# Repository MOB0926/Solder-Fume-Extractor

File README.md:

# Solder-Fume-Extractor

# Why?

- I made this project because I needed a fan extarctor in general and thought it would be fun to just make one as a project for Blueprint, in my effrot to gain experience in engeneering and design.

# What?

- This project is my attempt at making a custom fume extractor using a 120mm pc fan and a custom PCB.
   
- In order to not waste a full MCU on just a fan I opted to add a few features and make this fan feature a rotary encoder, OLED display, and GPIO pins for working on projects.
        
- The fan and PCB are housed in a custom 3D-Printed case using some pc fan mounting screws
       
- My original goal with the design was to make it a economic as possible, but with the nesscesity of a custom PCB I opted instead to focus my main goal on hand-soldering the PCB, which is something I have been wanting to learn. 
        
# Case
       
- The design began with the case, which i brainstormed untill i developed a general idea in my head.
   
- Once i had a general idea I began taking measurements and designing every piece in Onshape.
   
- I started with the main body, keeping in mind space and acces to the PCB and a way to mount the fan.

- I whent with a panel at the bottom, and slots on the sides which would hold the post that supported the fan.

- After I was done with the base, I needed a way to mount the fan and add a filter to stop myself from touching the blades.
           
- I decided on a casing that would wrap around the fan and allow me to mount it to the posts, and a custom honey-comb filter

- Finally I inserted all my parts into an assembly where I put everything together

# PCB

- I made the case first in order to figure out the dimmensions of the PCB I would be able to include.
   
- My original idea was to use an rp2040 as I have experience with it and a very over complicated adjustable boost converter to power the fan, but it was too much for me and I was unable to verify it would work before finishing the project, so I completely restructured my PCB in a V2
     
- V2: This version is much more simple and includes all hand-solder friendly components in order to acomplish my goal. I opted for an ESP32 module and a basic 5 to 12 volt boost converter.

# Firmware
         
- This design does not require any firmare to work because of how the PCB works but you can digitally disable the fan through a mosfet (using IO6 on the MCU). I made google Gemini write me a quick c++ script for it which is placed in the code.txt file
       
- This board can use other languages like CircuitPython using the (ESP32-C3-Lyra V2.0 by Espressif) release as it uses the same MCU so it should work fine. But you can use whatever suits your project.

# Cost

- PCB: $2.10 (plus shipping)
- PCB Components: $19.19 (plus shipping)
- PC Fan: $10-$30 (or free if you have a spare one)
- PC Fan Mounting Screws: $5 (or free if you have a PC with spares)
- 3D-Printing Fillament: (unknown yet)

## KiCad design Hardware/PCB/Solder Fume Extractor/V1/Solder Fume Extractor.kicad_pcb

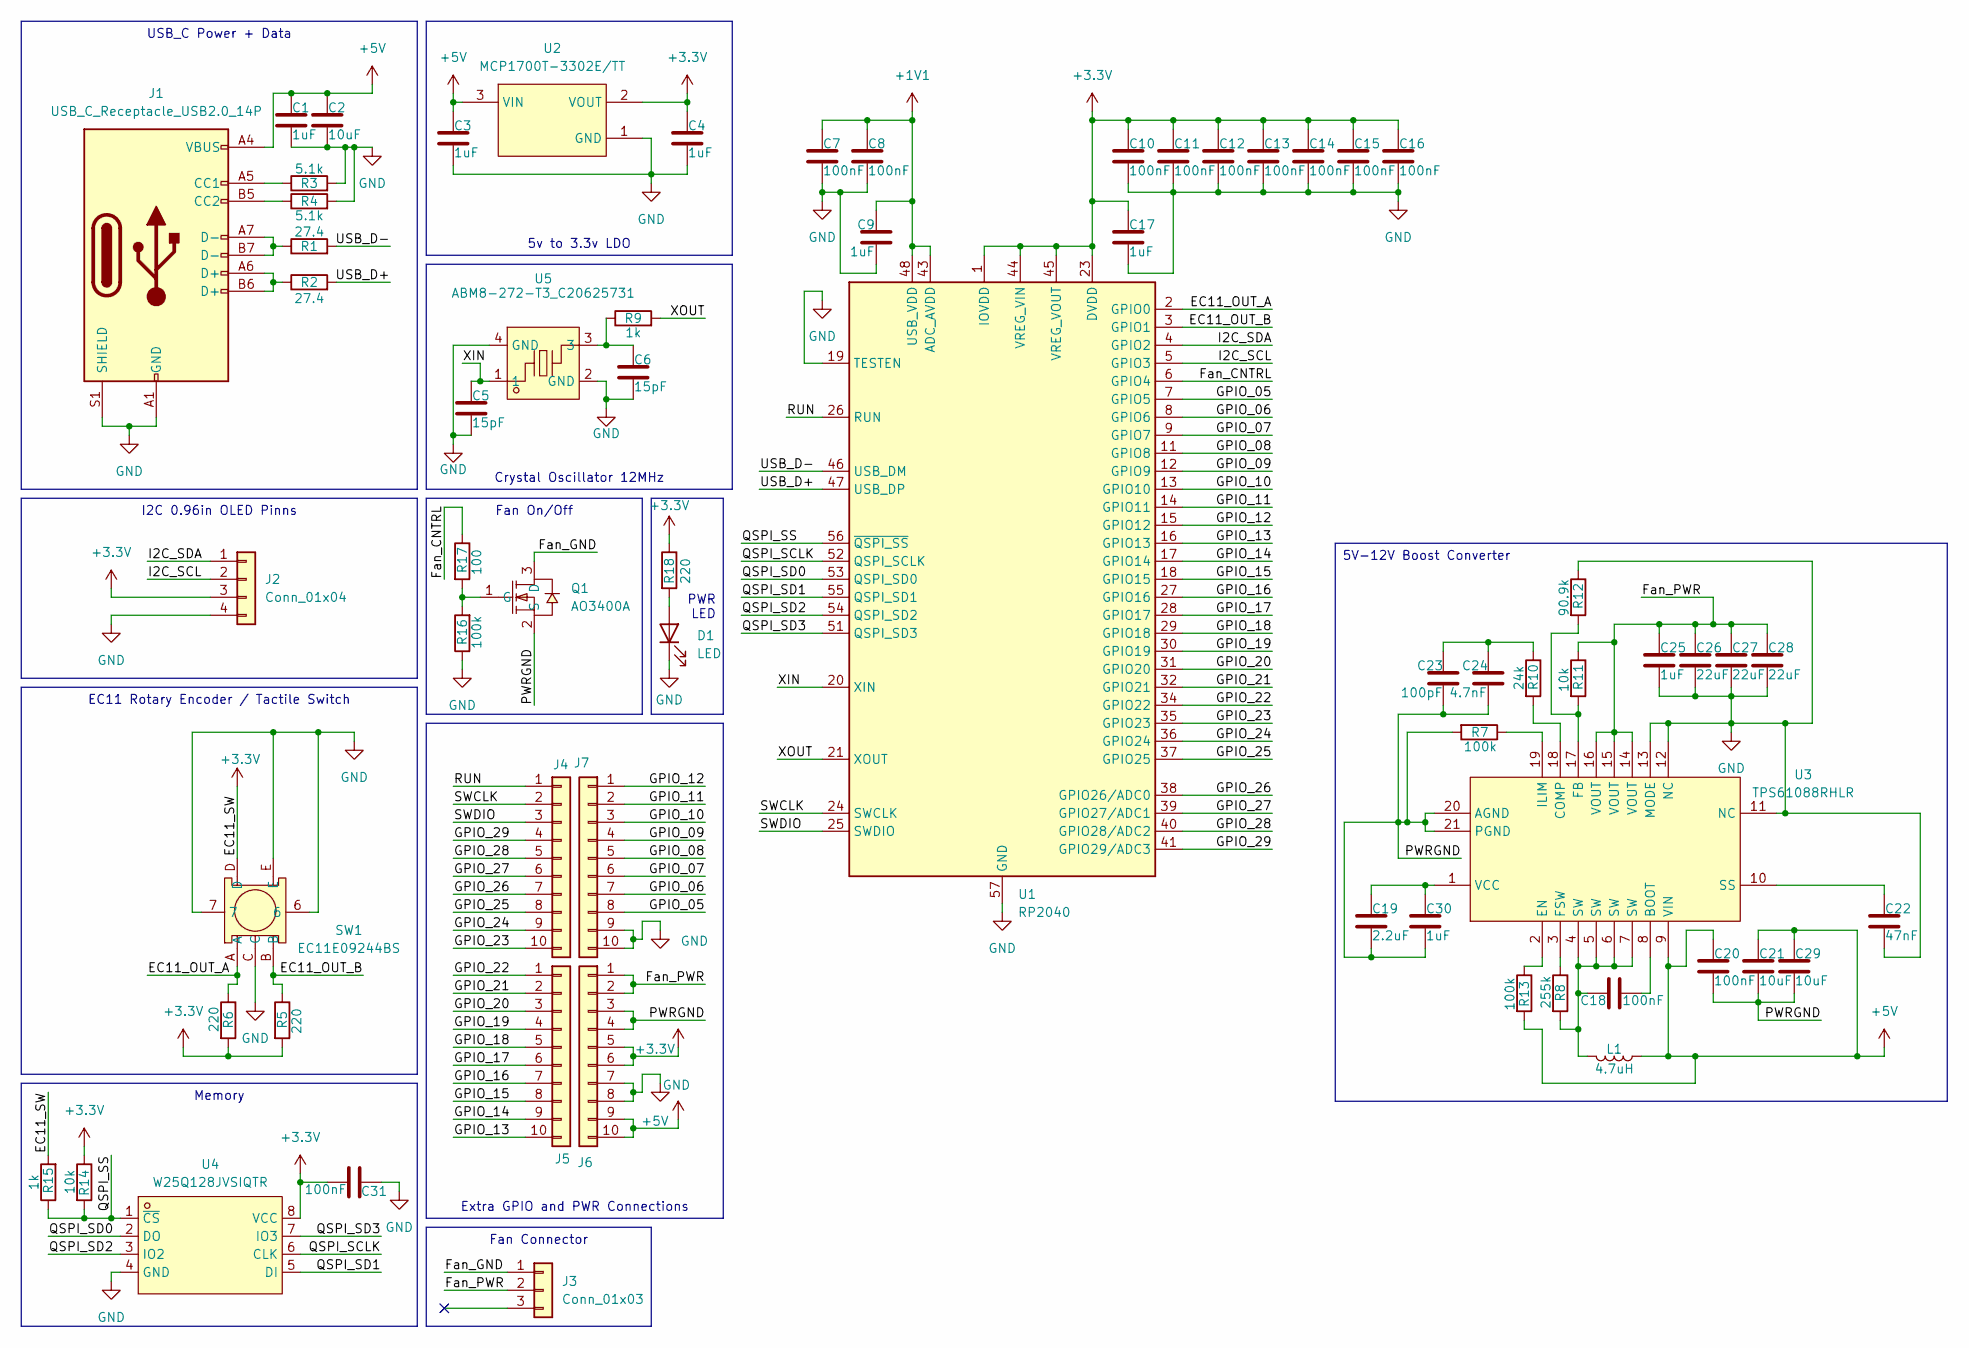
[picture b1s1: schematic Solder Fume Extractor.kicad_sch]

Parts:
C1, C3, C4, C9, C17, C25, C30: 1uF; C_0603_1608Metric
C2: 10uF; C_0603_1608Metric
C5, C6: 15pF; C_0603_1608Metric
C7, C8, C10, C11, C12, C13, C14, C15, C16, C18, C20, C31: 100nF; C_0603_1608Metric
C19: 2.2uF; C_0603_1608Metric
C21, C29: 10uF; C_1210_3225Metric
C22: 47nF; C_0603_1608Metric
C23: 100pF; C_0603_1608Metric
C24: 4.7nF; C_0603_1608Metric
C26, C27, C28: 22uF; C_1210_3225Metric
D1: LED; LED_0603_1608Metric
J1: USB_C_Receptacle_USB2.0_14P; USB_C_Receptacle_HRO_TYPE-C-31-M-12
J2: Conn_01x04; PinHeader_1x04_P2.54mm_Vertical
J3: Conn_01x03; PinHeader_1x03_P2.54mm_Vertical
J4, J5, J6, J7: Conn_01x10; PinHeader_1x10_P2.54mm_Vertical
L1: 4.7uH; L_Taiyo-Yuden_NR-60xx_HandSoldering
Q1: AO3400A; SOT-23-3_L2.9-W1.3-P1.90-LS2.4-BR; LCSC Part C20917
R1, R2: 27.4; R_0603_1608Metric
R3, R4: 5.1k; R_0603_1608Metric
R5, R6, R18: 220; R_0603_1608Metric
R7: 100k; C_0603_1608Metric
R8: 255k; R_0603_1608Metric
R9, R15: 1k; R_0603_1608Metric
R10: 24k; R_0603_1608Metric
R11, R14: 10k; R_0603_1608Metric
R12: 90.9k; R_0603_1608Metric
R13, R16: 100k; R_0603_1608Metric
R17: 100; R_0603_1608Metric
SW1: EC11E09244BS; SW-TH_EC11XXXXXXXX; LCSC Part C470742
U1: RP2040; QFN-56-1EP_7x7mm_P0.4mm_EP3.2x3.2mm
U2: MCP1700T-3302E/TT; SOT-23-3_L2.9-W1.6-P1.90-LS2.8-BR; LCSC Part C39051
U3: TPS61088RHLR; VQFN-20_L4.6-W3.6-P0.50-BL; LCSC Part C87357
U4: W25Q128JVSIQTR; SOIC-8_L5.3-W5.3-P1.27-LS8.0-BL; LCSC Part C97521
U5: ABM8-272-T3_C20625731; CRYSTAL-SMD_4P-L3.2-W2.5-BL; LCSC Part C20625731

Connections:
+1V1: C7.1, C8.1, C9.1, U1.43 (ADC_AVDD), U1.48 (USB_VDD)
+3.3V: C4.1, C10.1, C11.1, C12.1, C13.1, C14.1, C15.1, C16.1, C17.1, C31.2, J2.3, J6.5, J6.6, R5.2, R6.2, R14.1, R15.2, R18.1, SW1.D, U1.1 (IOVDD), U1.10 (IOVDD), U1.22 (IOVDD), U1.23 (DVDD), U1.33 (IOVDD), U1.42 (IOVDD), U1.44 (VREG_VIN), U1.45 (VREG_VOUT), U1.49 (IOVDD), U1.50 (DVDD), U2.2 (VOUT), U4.8 (VCC)
+5V: C1.1, C2.1, C3.1, C20.1, C21.1, C29.1, J1.A4 (VBUS), J1.A9 (VBUS), J1.B4 (VBUS), J1.B9 (VBUS), J6.9, J6.10, L1.2, R13.2, U2.3 (VIN), U3.9 (VIN)
/EC11_OUT_A: R6.1, SW1.A, U1.2 (GPIO0)
/EC11_OUT_B: R5.1, SW1.B, U1.3 (GPIO1)
/Fan_CNTRL: R17.1, U1.6 (GPIO4)
/Fan_GND: J3.1, Q1.3 (D)
/Fan_PWR: C25.1, C26.1, C27.1, C28.1, J3.2, J6.1, J6.2, R11.1, U3.14 (VOUT), U3.15 (VOUT), U3.16 (VOUT)
/GPIO_05: J7.8, U1.7 (GPIO5)
/GPIO_06: J7.7, U1.8 (GPIO6)
/GPIO_07: J7.6, U1.9 (GPIO7)
/GPIO_08: J7.5, U1.11 (GPIO8)
/GPIO_09: J7.4, U1.12 (GPIO9)
/GPIO_10: J7.3, U1.13 (GPIO10)
/GPIO_11: J7.2, U1.14 (GPIO11)
/GPIO_12: J7.1, U1.15 (GPIO12)
/GPIO_13: J5.10, U1.16 (GPIO13)
/GPIO_14: J5.9, U1.17 (GPIO14)
/GPIO_15: J5.8, U1.18 (GPIO15)
/GPIO_16: J5.7, U1.27 (GPIO16)
/GPIO_17: J5.6, U1.28 (GPIO17)
/GPIO_18: J5.5, U1.29 (GPIO18)
/GPIO_19: J5.4, U1.30 (GPIO19)
/GPIO_20: J5.3, U1.31 (GPIO20)
/GPIO_21: J5.2, U1.32 (GPIO21)
/GPIO_22: J5.1, U1.34 (GPIO22)
/GPIO_23: J4.10, U1.35 (GPIO23)
/GPIO_24: J4.9, U1.36 (GPIO24)
/GPIO_25: J4.8, U1.37 (GPIO25)
/GPIO_26: J4.7, U1.38 (GPIO26/ADC0)
/GPIO_27: J4.6, U1.39 (GPIO27/ADC1)
/GPIO_28: J4.5, U1.40 (GPIO28/ADC2)
/GPIO_29: J4.4, U1.41 (GPIO29/ADC3)
/I2C_SCL: J2.2, U1.5 (GPIO3)
/I2C_SDA: J2.1, U1.4 (GPIO2)
/PWRGND: C19.2, C20.2, C21.2, C23.2, C24.2, C29.2, C30.2, J6.3, J6.4, Q1.2 (S), R7.2, U3.20 (AGND), U3.21 (PGND)
/QSPI_SCLK: U1.52 (QSPI_SCLK), U4.6 (CLK)
/QSPI_SD0: U1.53 (QSPI_SD0), U4.2 (DO)
/QSPI_SD1: U1.55 (QSPI_SD1), U4.5 (DI)
/QSPI_SD2: U1.54 (QSPI_SD2), U4.3 (IO2)
/QSPI_SD3: U1.51 (QSPI_SD3), U4.7 (IO3)
/QSPI_SS: R14.2, R15.1, U1.56 (~QSPI_SS), U4.1 (~CS)
/RUN: J4.1, U1.26 (RUN)
/SWCLK: J4.2, U1.24 (SWCLK)
/SWDIO: J4.3, U1.25 (SWDIO)
/USB_D+: R2.2, U1.47 (USB_DP)
/USB_D-: R1.2, U1.46 (USB_DM)
/XIN: C5.1, U1.20 (XIN), U5.1
/XOUT: R9.2, U1.21 (XOUT)
GND: C1.2, C2.2, C3.2, C4.2, C5.2, C6.2, C7.2, C8.2, C9.2, C10.2, C11.2, C12.2, C13.2, C14.2, C15.2, C16.2, C17.2, C22.2, C25.2, C26.2, C27.2, C28.2, C31.1, D1.1 (K), J1.A1 (GND), J1.A12 (GND), J1.B1 (GND), J1.B12 (GND), J1.S1 (SHIELD), J2.4, J6.7, J6.8, J7.9, J7.10, R3.2, R4.2, R12.1, R16.1, SW1.6, SW1.7, SW1.C, SW1.E, U1.19 (TESTEN), U1.57 (GND), U2.1 (GND), U3.11 (NC), U3.12 (NC), U3.13 (MODE), U4.4 (GND), U5.2 (GND), U5.4 (GND)
unnamed: C6.1, R9.1, U5.3
unnamed: C18.1, L1.1, R8.2, U3.4 (SW), U3.5 (SW), U3.6 (SW), U3.7 (SW)
unnamed: C23.1, C24.1, R10.1
unnamed: D1.2 (A), R18.2
unnamed: J1.A5 (CC1), R3.1
unnamed: J1.B5 (CC2), R4.1
unnamed: J1.A6 (D+), J1.B6 (D+), R2.1
unnamed: J1.A7 (D-), J1.B7 (D-), R1.1
unnamed: Q1.1 (G), R16.2, R17.2
unnamed: C18.2, U3.8 (BOOT)
unnamed: R10.2, U3.18 (COMP)
unnamed: R13.1, U3.2 (EN)
unnamed: R11.2, R12.2, U3.17 (FB)
unnamed: R8.1, U3.3 (FSW)
unnamed: R7.1, U3.19 (ILIM)
unnamed: C22.1, U3.10 (SS)
unnamed: C19.1, C30.1, U3.1 (VCC)

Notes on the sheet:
Extra GPIO and PWR Connections
Crystal Oscillator 12MHz
I2C 0.96in OLED Pinns
PWR LED
5v to 3.3v LDO
Memory
USB_C Power + Data
Fan Connector
5V-12V Boost Converter
Fan On/Off
EC11 Rotary Encoder / Tactile Switch

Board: 2 copper layers, 65 parts (0 on the bottom side), 67 nets, no tracks yet.

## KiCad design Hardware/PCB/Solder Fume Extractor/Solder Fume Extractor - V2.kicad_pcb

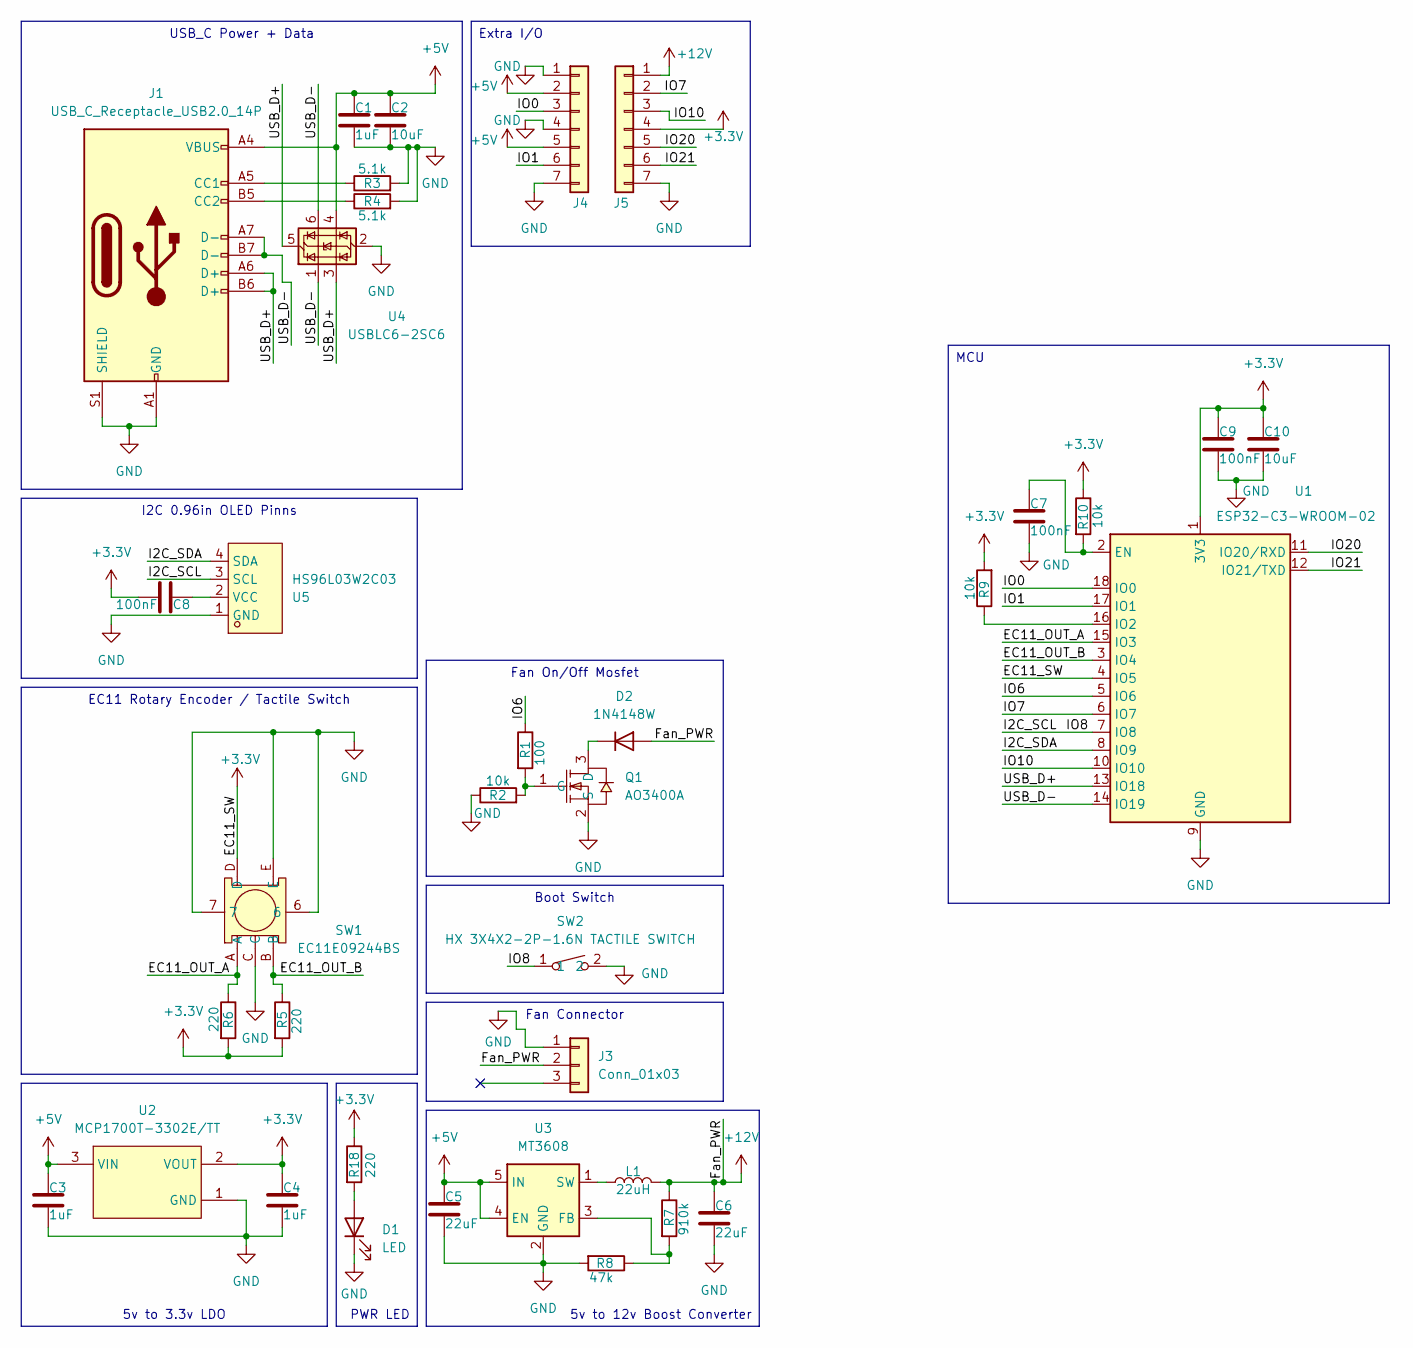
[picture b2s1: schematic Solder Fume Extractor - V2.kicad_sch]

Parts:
C1, C3, C4: 1uF; C_1206_3216Metric_Pad1.33x1.80mm_HandSolder
C2, C10: 10uF; C_1206_3216Metric_Pad1.33x1.80mm_HandSolder
C5, C6: 22uF; C_1206_3216Metric_Pad1.33x1.80mm_HandSolder
C7, C8, C9: 100nF; C_1206_3216Metric_Pad1.33x1.80mm_HandSolder
D1: LED; LED_1206_3216Metric_Pad1.42x1.75mm_HandSolder
D2: 1N4148W; D_SOD-123
J1: USB_C_Receptacle_USB2.0_14P; USB_C_Receptacle_HRO_TYPE-C-31-M-12
J3: Conn_01x03; PinHeader_1x03_P2.54mm_Vertical
J4, J5: Conn_01x07; PinHeader_1x07_P2.54mm_Vertical
L1: 22uH; IND-SMD_L5.7-W5.2
Q1: AO3400A; SOT-23-3_L2.9-W1.3-P1.90-LS2.4-BR; LCSC Part C20917
R1: 100; R_1206_3216Metric_Pad1.30x1.75mm_HandSolder
R2, R9, R10: 10k; R_1206_3216Metric_Pad1.30x1.75mm_HandSolder
R3, R4: 5.1k; R_1206_3216Metric_Pad1.30x1.75mm_HandSolder
R5, R6, R18: 220; R_1206_3216Metric_Pad1.30x1.75mm_HandSolder
R7: 910k; R_1206_3216Metric_Pad1.30x1.75mm_HandSolder
R8: 47k; R_1206_3216Metric_Pad1.30x1.75mm_HandSolder
SW1: EC11E09244BS; SW-TH_EC11XXXXXXXX; LCSC Part C470742
SW2: HX 3X4X2-2P-1.6N TACTILE SWITCH; KEY-SMD_L4.0-W3.0-LS4.9-1; LCSC Part C49234124
U1: ESP32-C3-WROOM-02
U2: MCP1700T-3302E/TT; SOT-23-3_L2.9-W1.6-P1.90-LS2.8-BR; LCSC Part C39051
U3: MT3608; SOT-23-6
U4: USBLC6-2SC6; SOT-23-6
U5: HS96L03W2C03; OLED-TH_L27.8-W27.2-P2.54_C9900033791; LCSC Part C5248080

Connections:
+3.3V: C4.1, C8.1, C9.1, C10.1, J5.4, R5.2, R6.2, R9.2, R10.1, R18.1, SW1.D, U1.1 (3V3), U1.4 (IO5), U2.2 (VOUT)
+5V: C1.1, C2.1, C3.1, C5.1, J1.A4 (VBUS), J1.A9 (VBUS), J1.B4 (VBUS), J1.B9 (VBUS), J4.2, J4.5, U2.3 (VIN), U3.4 (EN), U3.5 (IN), U4.4 (I/O2)
+12V: C6.1, D2.2 (A), J3.2, J5.1, L1.2, R7.1
/EC11_OUT_A: R6.1, SW1.A, U1.15 (IO3)
/EC11_OUT_B: R5.1, SW1.B, U1.3 (IO4)
/I2C_SCL: SW2.1, U1.7 (IO8), U5.3 (SCL)
/I2C_SDA: U1.8 (IO9), U5.4 (SDA)
/IO0: J4.3, U1.18 (IO0)
/IO1: J4.6, U1.17 (IO1)
/IO6: R1.1, U1.5 (IO6)
/IO7: J5.2, U1.6 (IO7)
/IO10: J5.3, U1.10 (IO10)
/IO20: J5.5, U1.11 (IO20/RXD)
/IO21: J5.6, U1.12 (IO21/TXD)
/USB_D+: J1.A6 (D+), J1.B6 (D+), U1.13 (IO18), U4.3 (I/O2), U4.5 (VBUS)
/USB_D-: J1.A7 (D-), J1.B7 (D-), U1.14 (IO19), U4.1 (I/O1), U4.6 (I/O1)
GND: C1.2, C2.2, C3.2, C4.2, C5.2, C6.2, C7.2, C9.2, C10.2, D1.1 (K), J1.A1 (GND), J1.A12 (GND), J1.B1 (GND), J1.B12 (GND), J1.S1 (SHIELD), J3.1, J4.1, J4.4, J4.7, J5.7, Q1.2 (S), R2.1, R3.2, R4.2, R8.2, SW1.6, SW1.7, SW1.C, SW1.E, SW2.2, U1.9 (GND), U1.19 (GND), U2.1 (GND), U3.2 (GND), U4.2 (GND), U5.1 (GND)
unnamed: D1.2 (A), R18.2
unnamed: D2.1 (K), Q1.3 (D)
unnamed: J1.A5 (CC1), R3.1
unnamed: J1.B5 (CC2), R4.1
unnamed: Q1.1 (G), R1.2, R2.2
unnamed: C7.1, R10.2, U1.2 (EN)
unnamed: R9.1, U1.16 (IO2)
unnamed: R7.2, R8.1, U3.3 (FB)
unnamed: L1.1, U3.1 (SW)
unnamed: C8.2, U5.2 (VCC)

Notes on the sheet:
I2C 0.96in OLED Pinns
PWR LED
5v to 3.3v LDO
MCU
5v to 12v Boost Converter
Boot Switch
Extra I/O
USB_C Power + Data
Fan Connector
Fan On/Off Mosfet
EC11 Rotary Encoder / Tactile Switch

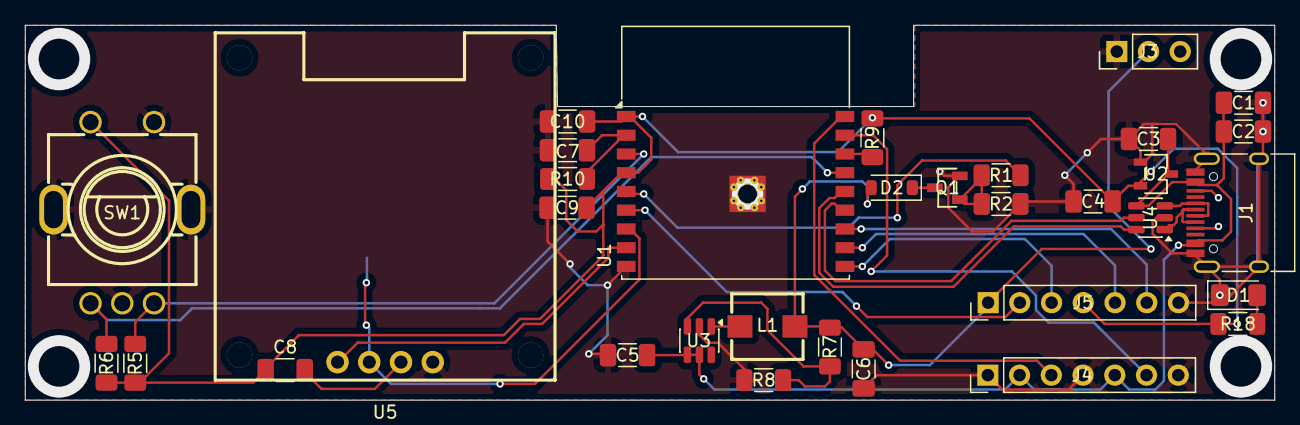
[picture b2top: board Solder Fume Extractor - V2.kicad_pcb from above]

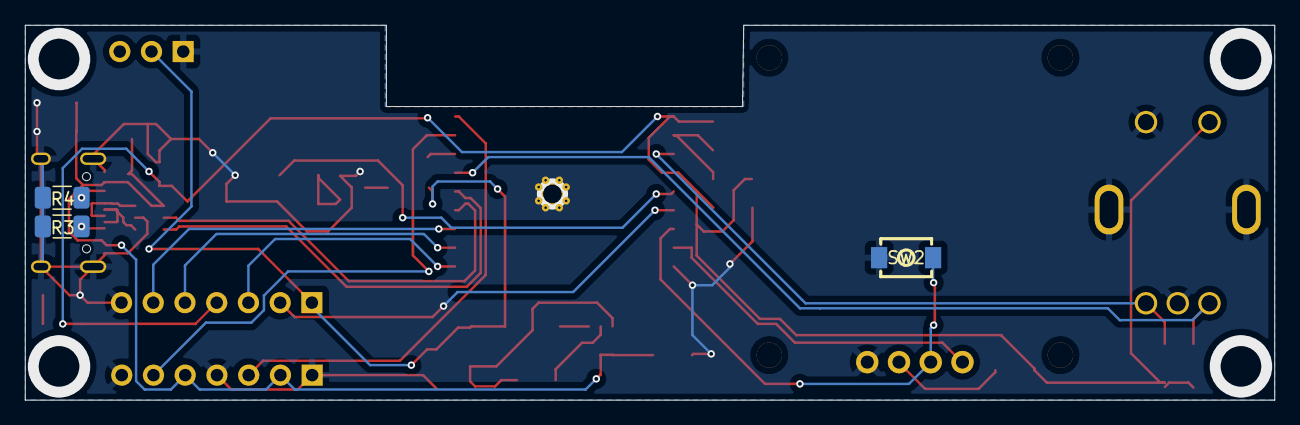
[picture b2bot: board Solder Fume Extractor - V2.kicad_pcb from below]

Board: 2 copper layers, 100.0 x 30.0 mm, 36 parts (3 on the bottom side), 27 nets.

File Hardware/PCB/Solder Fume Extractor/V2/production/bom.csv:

Designator,Footprint,Quantity,Value,LCSC Part #
"C1, C3, C4",1206,3,1uF,
"C10, C2",1206,2,10uF,
"C5, C6",1206,2,22uF,
"C7, C8, C9",1206,3,100nF,
D1,1206,1,LED,
D2,D_SOD-123,1,1N4148W,
J1,USB_C_Receptacle_HRO_TYPE-C-31-M-12,1,USB_C_Receptacle_USB2.0_14P,
J3,PinHeader_1x03_P2.54mm_Vertical,1,Conn_01x03,
"J4, J5",PinHeader_1x07_P2.54mm_Vertical,2,Conn_01x07,
L1,IND-SMD_L5.7-W5.2,1,22uH,
Q1,SOT-23-3_L2.9-W1.3-P1.90-LS2.4-BR,1,AO3400A,C20917
R1,1206,1,100,
"R10, R2, R9",1206,3,10k,
"R18, R5, R6",1206,3,220,
"R3, R4",1206,2,5.1k,
R7,1206,1,910k,
R8,1206,1,47k,
SW1,SW-TH_EC11XXXXXXXX,1,EC11E09244BS,C470742
SW2,KEY-SMD_L4.0-W3.0-LS4.9-1,1,HX 3X4X2-2P-1.6N TACTILE SWITCH,C49234124
U1,ESP32-C3-WROOM-02,1,ESP32-C3-WROOM-02,
U2,SOT-23-3_L2.9-W1.6-P1.90-LS2.8-BR,1,MCP1700T-3302E/TT,C39051
U3,SOT-23-6,1,MT3608,
U4,SOT-23-6,1,USBLC6-2SC6,
U5,OLED-TH_L27.8-W27.2-P2.54_C9900033791,1,HS96L03W2C03,C5248080

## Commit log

2026-03-16 PCB Complete
    The PCB Schematic and Design is complete. Revision will be made to the aesthetic (Adding silkscreen and labeling parts)
2026-03-26 README
    Expanded the README to include project motivation, design details, PCB information, firmware notes, and cost breakdown.
2026-03-26 Design Done
2026-03-26 Now design done
